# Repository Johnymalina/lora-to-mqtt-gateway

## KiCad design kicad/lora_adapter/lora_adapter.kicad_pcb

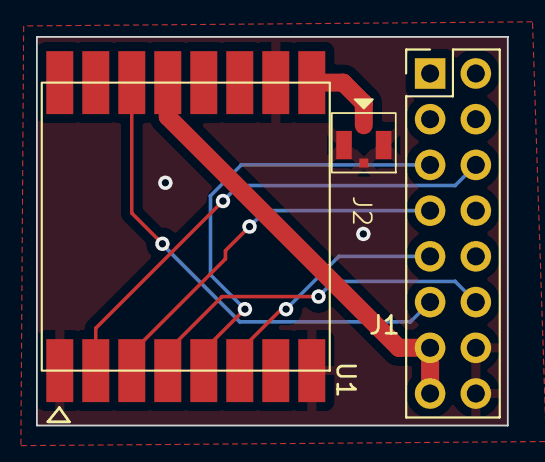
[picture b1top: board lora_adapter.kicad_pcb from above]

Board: 2 copper layers, 26.2 x 21.6 mm, 3 parts (0 on the bottom side), 9 nets.

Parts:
J1: Conn_02x08_Odd_Even; PinHeader_2x08_P2.54mm_Vertical
J2: Conn_Coaxial; IPX4_antena
U1: RFM9X; rfmxx_lora_module

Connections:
+3.3V: J1.13, J1.15, U1.13 (3.3V)
DIO0: J1.11, U1.14 (DIO0)
GND: J1.14, J1.16, J2.2 (Ext), U1.1 (GND), U1.8 (GND), U1.10 (GND)
MISO: J1.6, U1.2 (MISO)
MOSI: J1.7, U1.3 (MOSI)
NSS: J1.5, U1.5 (NSS)
unnamed: J2.1 (In), U1.9 (ANT)
RST: J1.9, U1.6 (RESET)
SCK: J1.12, U1.4 (SCK)

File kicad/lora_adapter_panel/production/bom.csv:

Designator,Footprint,Quantity,Value,LCSC Part #
"J1_12, J1_11, J1_10, J1_9, J1_8, J1_7, J1_6, J1_5, J1_4, J1_3, J1_2, J1",PinHeader_2x08_P2.54mm_Vertical,12,Conn_02x08_Odd_Even,
"J2_12, J2_11, J2_10, J2_9, J2_8, J2_7, J2_6, J2_5, J2_4, J2_3, J2_2, J2",IPX4_antena,12,Conn_Coaxial,
"U1_12, U1_11, U1_10, U1_9, U1_8, U1_7, U1_6, U1_5, U1_4, U1_3, U1_2, U1",rfmxx_lora_module,12,RFM9X,

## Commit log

2023-08-27 added libs
2023-08-27 wifi init
2023-08-27 debug
2023-08-27 lora init and receive
2023-08-27 smqtt setup
2023-08-27 debug init
2023-08-27 debug lines
2023-08-30 debug msgs
2023-09-09 lora to mqtt working
2023-09-13 mqtt working
2023-09-24 added html status page template
2023-09-24 rm json variable
2023-09-24 added html file
2023-09-24 lora separated from main code
2023-09-24 wifi and mqtt separated
2023-09-24 html static page added
2023-09-24 status change on web
2023-09-24 rm wlan file
2023-09-24 mqtt file rm
2023-09-24 lora rm
2023-09-24 rm Website file
2023-09-24 lora functions edited
2023-09-24 publishing of website
2023-09-24 add refresh to html
2023-09-24 mqtt connected check
2023-09-24 connected status update
2023-09-24 rm line
2023-09-25 change html code
2023-09-25 add refresh and function to show status
2023-09-25 chnge interval to refresh
2023-09-25 add debug
2023-10-07 changed pins for ttgo poe
2023-10-07 created LORA adapter
2023-10-07 lora callback
2023-10-07 step back before call back
2023-10-07 lora adapter updated
2023-10-09 remove not Lora code
2023-10-09 callback lora
2023-10-09 format change
2023-10-09 MQTT publish
2023-10-10 added json lib
2023-10-10 change pin
2023-10-10 data source and end device check
2023-10-10 added test device and workspace
2023-10-10 gtw status
2023-10-10 rm code
2023-10-21 liligo poe
2023-10-26 ethernet support
2023-11-12 updated pcbs
2024-03-31 created config.h
2024-04-01 web files
2024-04-01 edit colour
2024-04-01 logo updated
2024-04-01 config.h
2024-04-01 lora definition
2024-04-01 rm logo
2024-04-01 debug initialize
2024-04-01 removed WIFI for OTA
2024-04-02 added data
2024-04-02 added async web libs
2024-04-02 debug class
2024-04-02 comment rm
2024-04-03 added ota,web libs
2024-04-03 ota avalaible
2024-04-04 compiled. works?
2024-04-06 env name
2024-04-06 debug obj edit
2024-04-06 wokwi test files
2024-04-06 commented new ETH #defines
2024-04-07 simplyfy eth.begin
2024-04-07 ethernet connected
2024-04-07 rm callback network
2024-04-07 static page
2024-04-07 updated web look
2024-04-07 enviroment
2024-04-07 wifi events
2024-04-08 wifi events working
2024-04-08 added callback fn
2024-04-08 debug changed
2024-04-08 signature
2024-04-08 show full debug
2024-04-08 network debug msgs
2024-04-13 pub sub lib
2024-04-13 headder mqtt
2024-04-13 mqtt connection
2024-04-13 mqtt publish fn
2024-04-13 rm comments
2024-04-13 to dos
2024-04-14 WOKWI RM
2024-04-14 lora lib add
2024-04-14 lora headder
2024-04-14 debug msg
2024-04-14 back debln
2024-04-14 rearange
2024-04-14 lora begin
2024-04-14 lora receive msgs
2024-04-15 webserial lib
2024-04-15 add webserial
2024-04-15 added webserial
2024-04-15 webserial
2024-04-15 webserial debug
2024-04-15 webui changes added webserial and reboot buttons
2024-04-15 open links in new windows
2024-04-15 reboot request
2024-04-15 fromat
2024-04-15 delay serial
2024-04-16 format
2024-04-18 json handler added
2024-04-18 get status mqtt
2024-04-18 lora getStatus
2024-04-18 gateway status publish
2024-04-19 status
2024-04-21 serialized json to chararray
2024-04-21 publish status and received loradata
2024-04-21 added config file with lora adresses
2024-04-21 json dynamic document
2024-04-21 lora dresses
2024-04-21 extract addresses from json
2024-04-21 addresses check
2024-04-21 address list
2024-04-21 adress extraction
2024-04-21 config parameter to separate file
2024-04-21 Revert "config parameter to separate file"
    This reverts commit 097f02c29c160cc0a4bbdf6591588967ebcd0ab0.
2024-04-21 working merge from beta
2024-04-22 web handling
2024-04-22 added ip to gtw status
2024-04-22 default webpage
2024-04-22 rm web handler
2024-04-22 web page
2024-04-22 favicon, connstatus, ip address
2024-04-22 rm last received msgs
2024-04-22 logo rename resize
